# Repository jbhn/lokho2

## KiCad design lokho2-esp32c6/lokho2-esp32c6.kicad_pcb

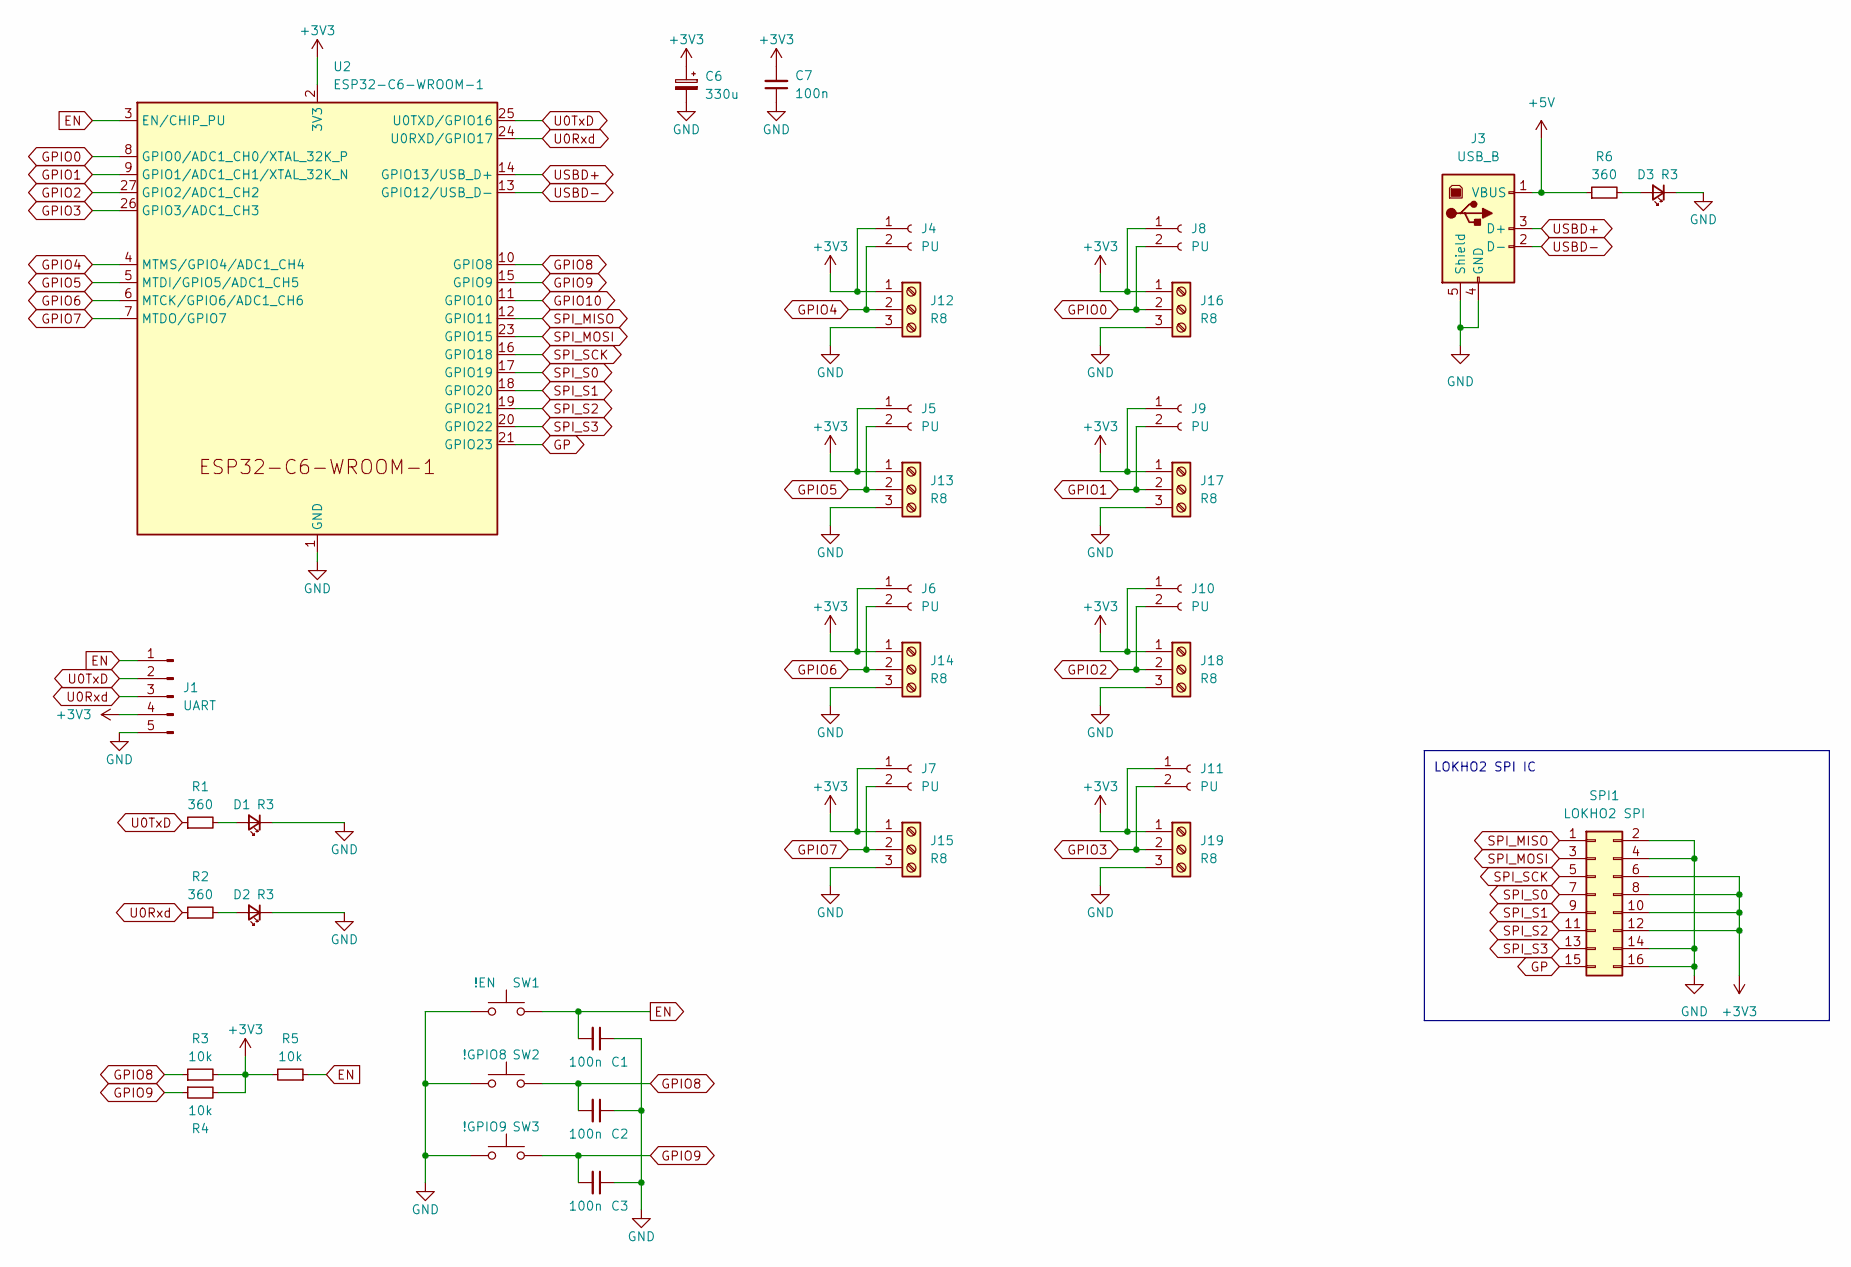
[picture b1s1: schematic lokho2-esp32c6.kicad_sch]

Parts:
C1, C2, C3, C7: 100n; C_Disc_D5.0mm_W2.5mm_P5.00mm
C6: 330u; CP_Radial_D8.0mm_P3.50mm
D1, D2, D3: R3; LED_D3.0mm
J1: UART; PinHeader_1x05_P2.54mm_Horizontal
J3: USB_B; USB_B_Lumberg_2411_02_Horizontal
J4, J5, J6, J7, J8, J9, J10, J11: PU; PinSocket_1x02_P2.54mm_Vertical
J12, J13, J14, J15, J16, J17, J18, J19: R8; TerminalBlock_4Ucon_1x03_P3.50mm_Horizontal
R1, R2, R6: 360; R_Axial_DIN0204_L3.6mm_D1.6mm_P7.62mm_Horizontal
R3, R4, R5: 10k; R_Axial_DIN0204_L3.6mm_D1.6mm_P7.62mm_Horizontal
SPI1: LOKHO2 SPI; IDC-Header_2x08_P2.54mm_Horizontal
SW1: !EN; SW_PUSH_6mm
SW2: !GPIO8; SW_PUSH_6mm
SW3: !GPIO9; SW_PUSH_6mm
U2: ESP32-C6-WROOM-1

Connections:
+3V3: C6.1, C7.2, J1.4, J4.1, J5.1, J6.1, J7.1, J8.1, J9.1, J10.1, J11.1, J12.1, J13.1, J14.1, J15.1, J16.1, J17.1, J18.1, J19.1, R3.2, R4.2, R5.2, SPI1.6, SPI1.8, SPI1.10, SPI1.12, U2.2 (3V3)
+5V: J3.1 (VBUS), R6.1
EN: C1.2, J1.1, R5.1, SW1.2, U2.3 (EN/CHIP_PU)
GND: C1.1, C2.1, C3.1, C6.2, C7.1, D1.1 (K), D2.1 (K), D3.1 (K), J1.5, J3.4 (GND), J3.5 (Shield), J12.3, J13.3, J14.3, J15.3, J16.3, J17.3, J18.3, J19.3, SPI1.2, SPI1.4, SPI1.14, SPI1.16, SW1.1, SW2.1, SW3.1, U2.1 (GND), U2.28 (GND), U2.29 (GND)
GP: SPI1.15, U2.21 (GPIO23)
GPIO0: J8.2, J16.2, U2.8 (GPIO0/ADC1_CH0/XTAL_32K_P)
GPIO1: J9.2, J17.2, U2.9 (GPIO1/ADC1_CH1/XTAL_32K_N)
GPIO2: J10.2, J18.2, U2.27 (GPIO2/ADC1_CH2)
GPIO3: J11.2, J19.2, U2.26 (GPIO3/ADC1_CH3)
GPIO4: J4.2, J12.2, U2.4 (MTMS/GPIO4/ADC1_CH4)
GPIO5: J5.2, J13.2, U2.5 (MTDI/GPIO5/ADC1_CH5)
GPIO6: J6.2, J14.2, U2.6 (MTCK/GPIO6/ADC1_CH6)
GPIO7: J7.2, J15.2, U2.7 (MTDO/GPIO7)
GPIO8: C2.2, R3.1, SW2.2, U2.10 (GPIO8)
GPIO9: C3.2, R4.1, SW3.2, U2.15 (GPIO9)
GPIO10: U2.11 (GPIO10)
unnamed: D1.2 (A), R1.2
unnamed: D2.2 (A), R2.2
unnamed: D3.2 (A), R6.2
SPI_MISO: SPI1.1, U2.12 (GPIO11)
SPI_MOSI: SPI1.3, U2.23 (GPIO15)
SPI_S0: SPI1.7, U2.17 (GPIO19)
SPI_S1: SPI1.9, U2.18 (GPIO20)
SPI_S2: SPI1.11, U2.19 (GPIO21)
SPI_S3: SPI1.13, U2.20 (GPIO22)
SPI_SCK: SPI1.5, U2.16 (GPIO18)
U0Rxd: J1.3, R2.1, U2.24 (U0RXD/GPIO17)
U0TxD: J1.2, R1.1, U2.25 (U0TXD/GPIO16)
USBD+: J3.3 (D+), U2.14 (GPIO13/USB_D+)
USBD-: J3.2 (D-), U2.13 (GPIO12/USB_D-)

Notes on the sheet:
LOKHO2 SPI IC

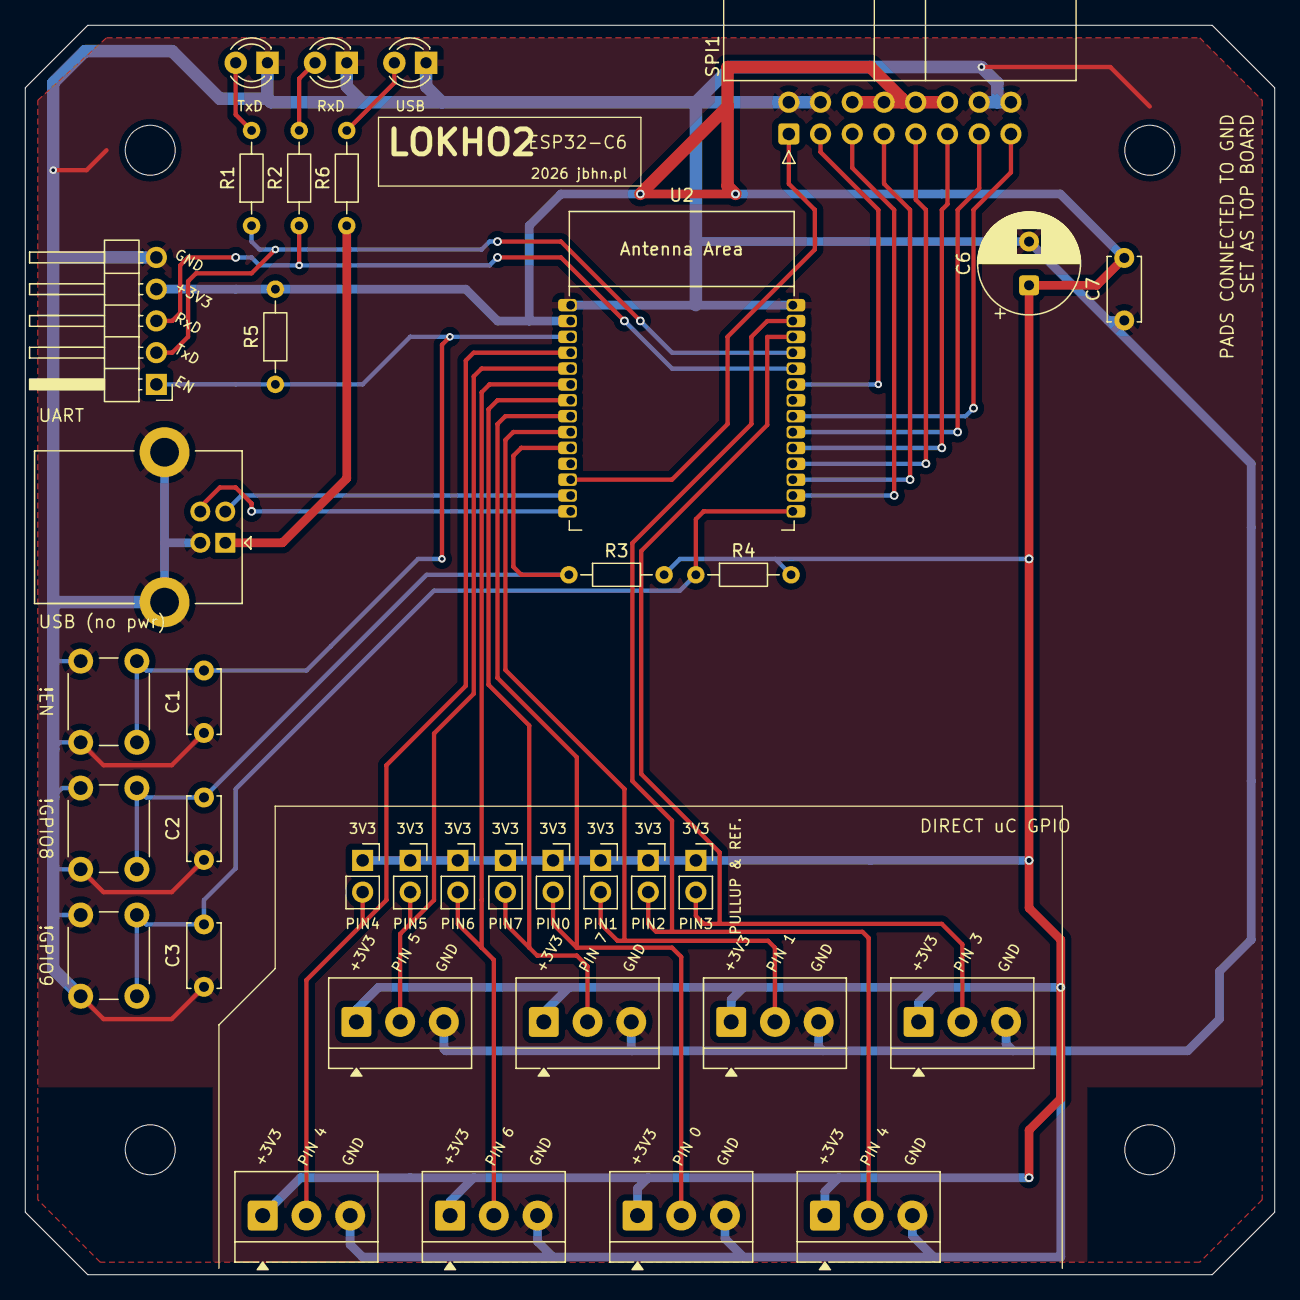
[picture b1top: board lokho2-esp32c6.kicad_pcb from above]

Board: 2 copper layers, 100.0 x 100.0 mm, 37 parts (0 on the bottom side), 29 nets.

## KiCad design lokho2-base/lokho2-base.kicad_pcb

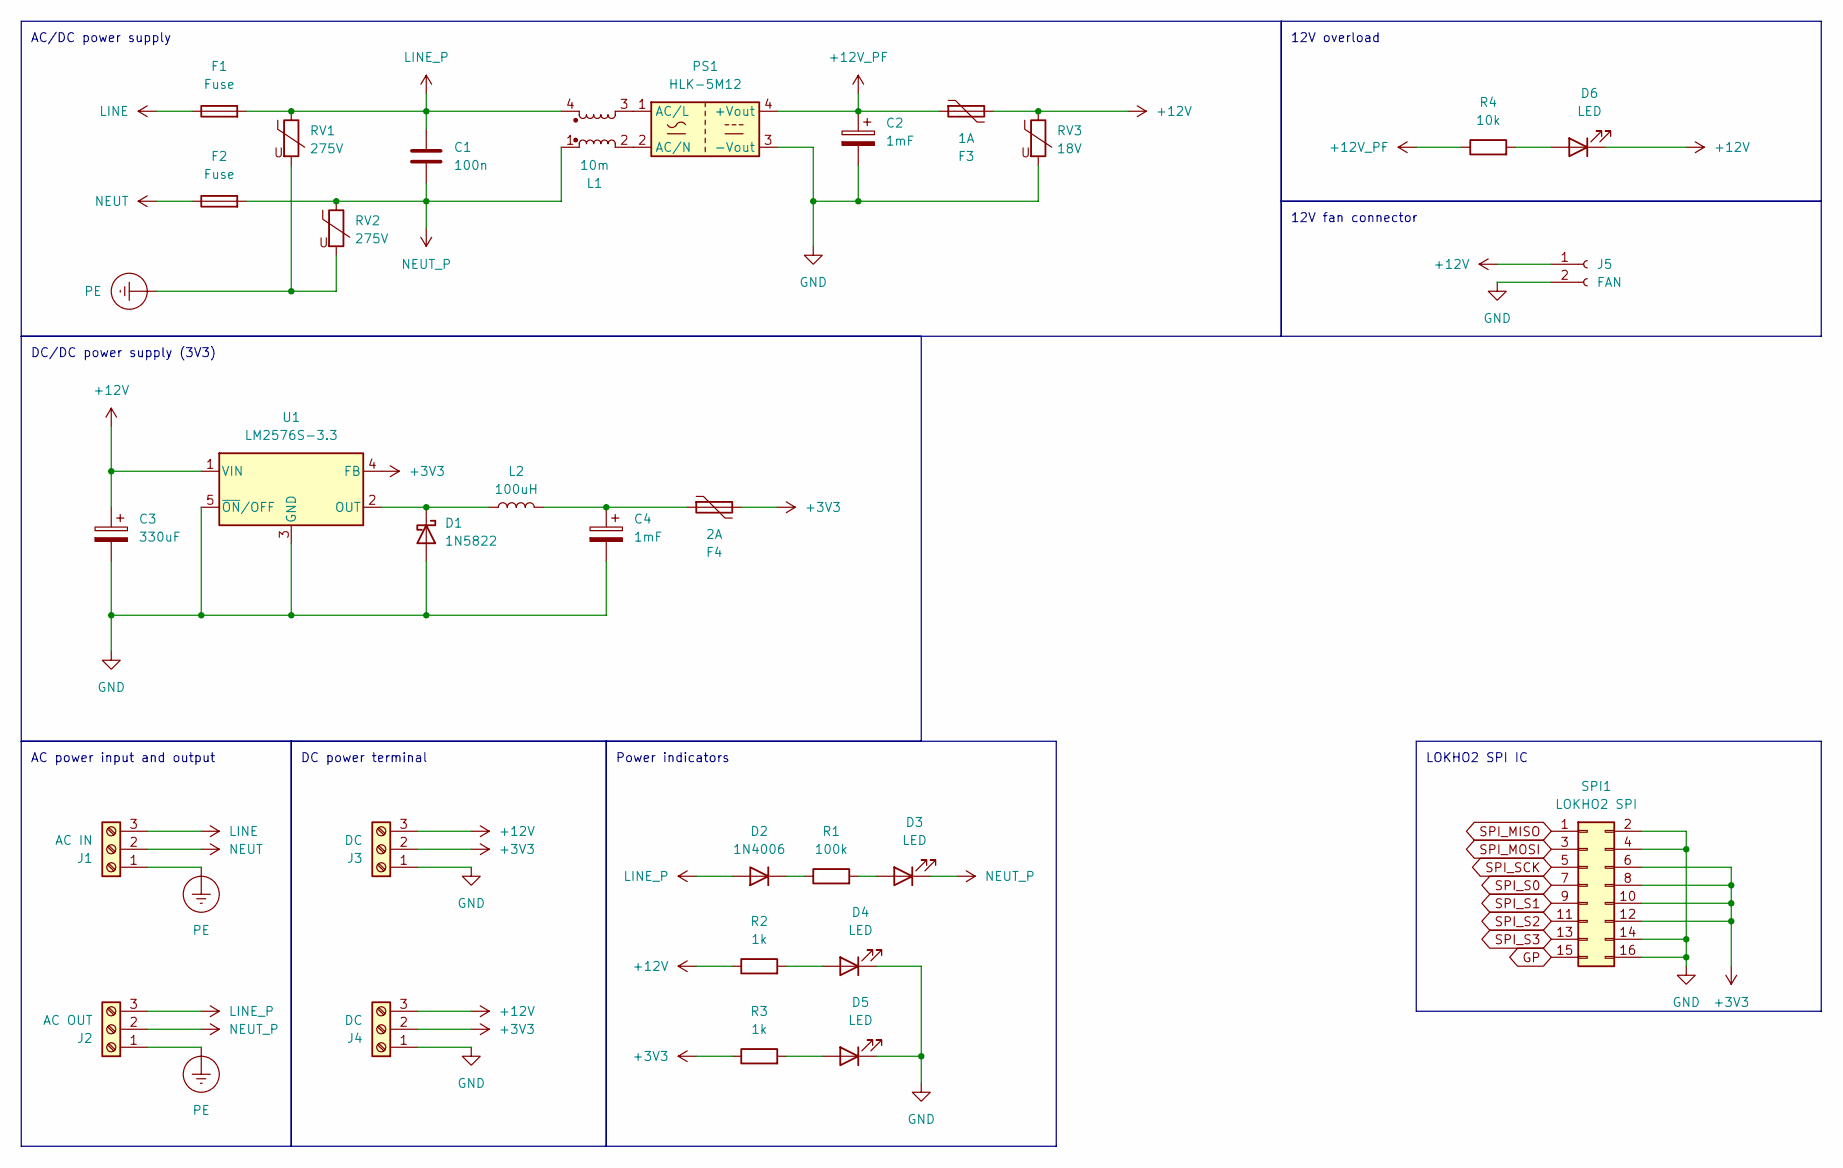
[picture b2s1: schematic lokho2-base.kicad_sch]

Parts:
C1: 100n; C_Rect_L11.5mm_W6.9mm_P10.00mm_MKT
C2, C4: 1mF; CP_Radial_D10.0mm_P5.00mm
C3: 330uF; CP_Radial_D8.0mm_P3.50mm
D1: 1N5822; D_DO-201AD_P15.24mm_Horizontal
D2: 1N4006; D_DO-41_SOD81_P10.16mm_Horizontal
D3, D4, D5: LED; LED_D3.0mm_Horizontal_O1.27mm_Z2.0mm
D6: LED; LED_D3.0mm
F1, F2: Fuse; Fuseholder_Clip-5x20mm_Littelfuse_100_Inline_P20.50x4.60mm_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
F3: 1A; C_Disc_D8.0mm_W2.5mm_P5.00mm
F4: 2A; C_Disc_D8.0mm_W2.5mm_P5.00mm
J1: AC IN; TerminalBlock_4Ucon_1x03_P3.50mm_Horizontal
J2: AC OUT; TerminalBlock_4Ucon_1x03_P3.50mm_Horizontal
J3, J4: DC; TerminalBlock_4Ucon_1x03_P3.50mm_Horizontal
J5: FAN; PinHeader_1x02_P2.54mm_Horizontal
L1: 10m; L_CommonMode_Toroid_Vertical_L22.0mm_W12.0mm_Px9.00mm_Py8.0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
L2: 100uH; L_Radial_D12.0mm_P5.00mm_Fastron_11P
PS1: HLK-5M12; Converter_ACDC_Hi-Link_HLK-5Mxx
R1: 100k; R_Axial_DIN0204_L3.6mm_D1.6mm_P7.62mm_Horizontal
R2, R3: 1k; R_Axial_DIN0204_L3.6mm_D1.6mm_P7.62mm_Horizontal
R4: 10k; R_Axial_DIN0204_L3.6mm_D1.6mm_P7.62mm_Horizontal
RV1, RV2: 275V; RV_Disc_D21.5mm_W4.3mm_P10mm
RV3: 18V; RV_Disc_D7mm_W3.4mm_P5mm
SPI1: LOKHO2 SPI; IDC-Header_2x08_P2.54mm_Horizontal
U1: LM2576S-3.3; TO-263-5_TabPin3

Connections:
+3V3: F4.2, J3.2, J4.2, R3.1, SPI1.6, SPI1.8, SPI1.10, SPI1.12, U1.4 (FB)
+12V: C3.1, D6.1 (K), F3.2, J3.3, J4.3, J5.1, R2.1, RV3.1, U1.1 (VIN)
+12V_PF: C2.1, F3.1, PS1.4 (+Vout), R4.1
GND: C2.2, C3.2, C4.2, D1.2 (A), D4.1 (K), D5.1 (K), J3.1, J4.1, J5.2, PS1.3 (-Vout), RV3.2, SPI1.2, SPI1.4, SPI1.14, SPI1.16, U1.3 (GND), U1.5 (~ON/OFF)
GP: SPI1.15
LINE: F1.1, J1.3
LINE_P: C1.1, D2.2 (A), F1.2, J2.3, L1.4, RV1.1
NEUT: F2.1, J1.2
NEUT_P: C1.2, D3.1 (K), F2.2, J2.2, L1.1, RV2.1
unnamed: C4.1, F4.1, L2.2
unnamed: D1.1 (K), L2.1, U1.2 (OUT)
unnamed: D2.1 (K), R1.1
unnamed: D3.2 (A), R1.2
unnamed: D4.2 (A), R2.2
unnamed: D5.2 (A), R3.2
unnamed: D6.2 (A), R4.2
unnamed: L1.3, PS1.1 (AC/L)
unnamed: L1.2, PS1.2 (AC/N)
PE: J1.1, J2.1, RV1.2, RV2.2
SPI_MISO: SPI1.1
SPI_MOSI: SPI1.3
SPI_S0: SPI1.7
SPI_S1: SPI1.9
SPI_S2: SPI1.11
SPI_S3: SPI1.13
SPI_SCK: SPI1.5

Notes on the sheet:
DC power terminal
12V fan connector
DC/DC power supply (3V3)
AC/DC power supply
AC power input and output
LOKHO2 SPI IC
Power indicators
12V overload

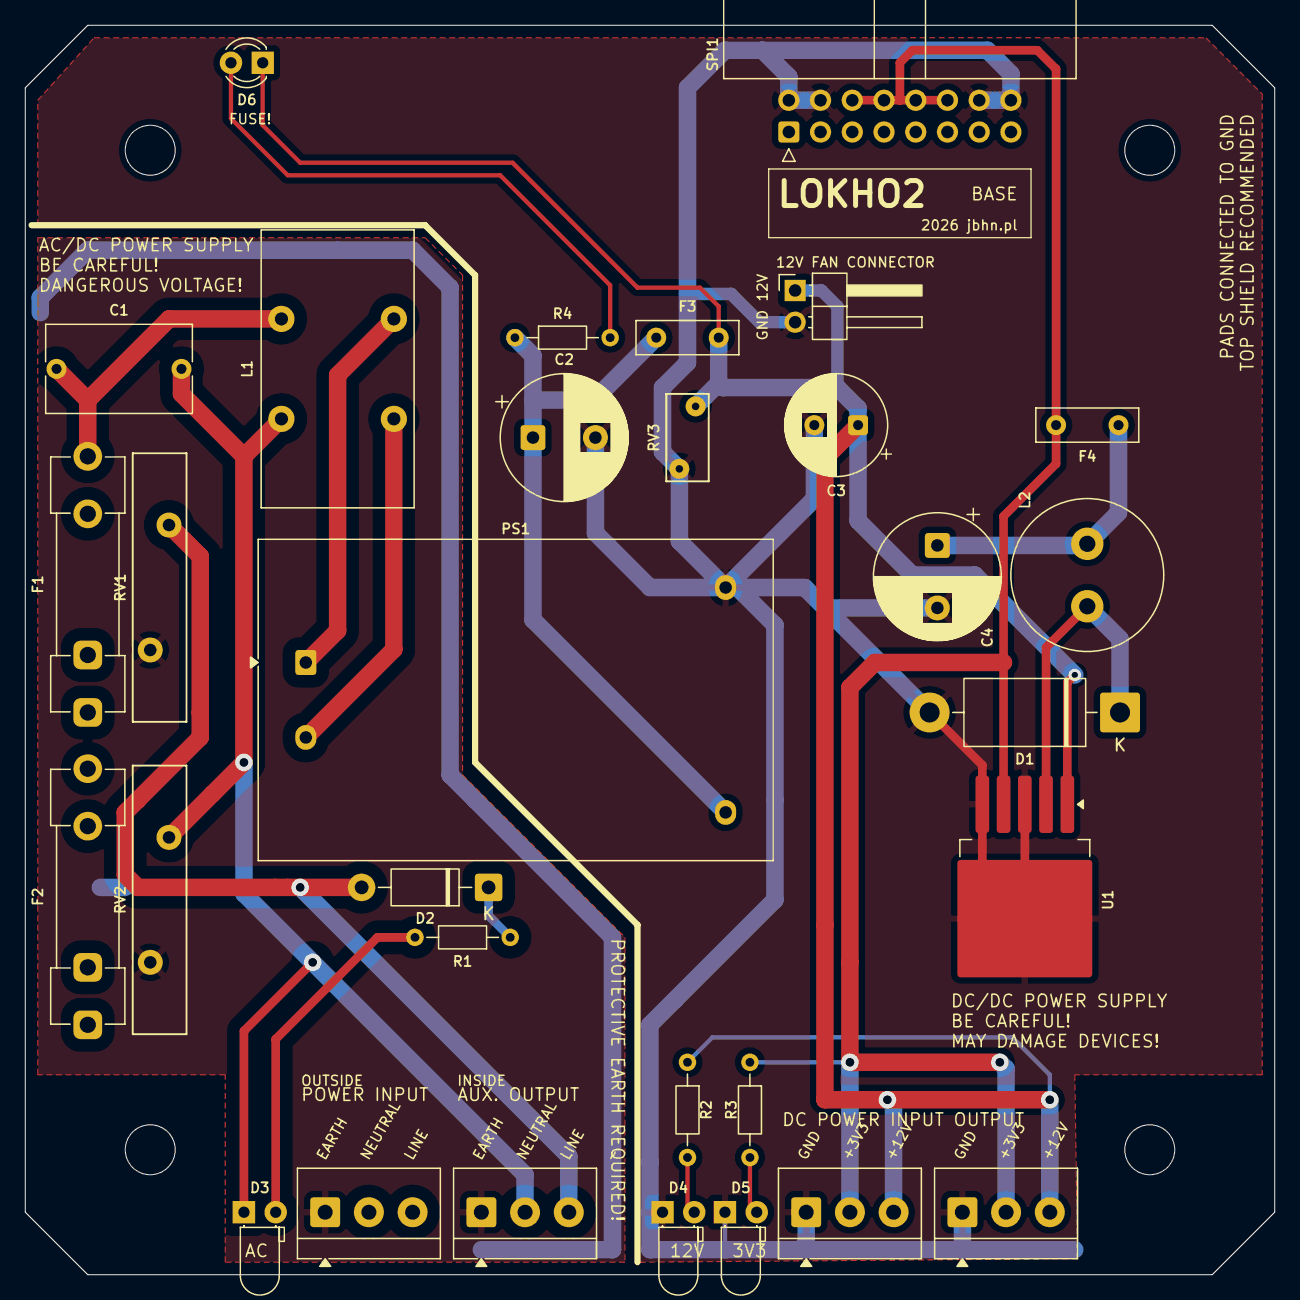
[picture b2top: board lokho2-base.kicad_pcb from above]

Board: 2 copper layers, 100.0 x 100.0 mm, 31 parts (0 on the bottom side), 18 nets.

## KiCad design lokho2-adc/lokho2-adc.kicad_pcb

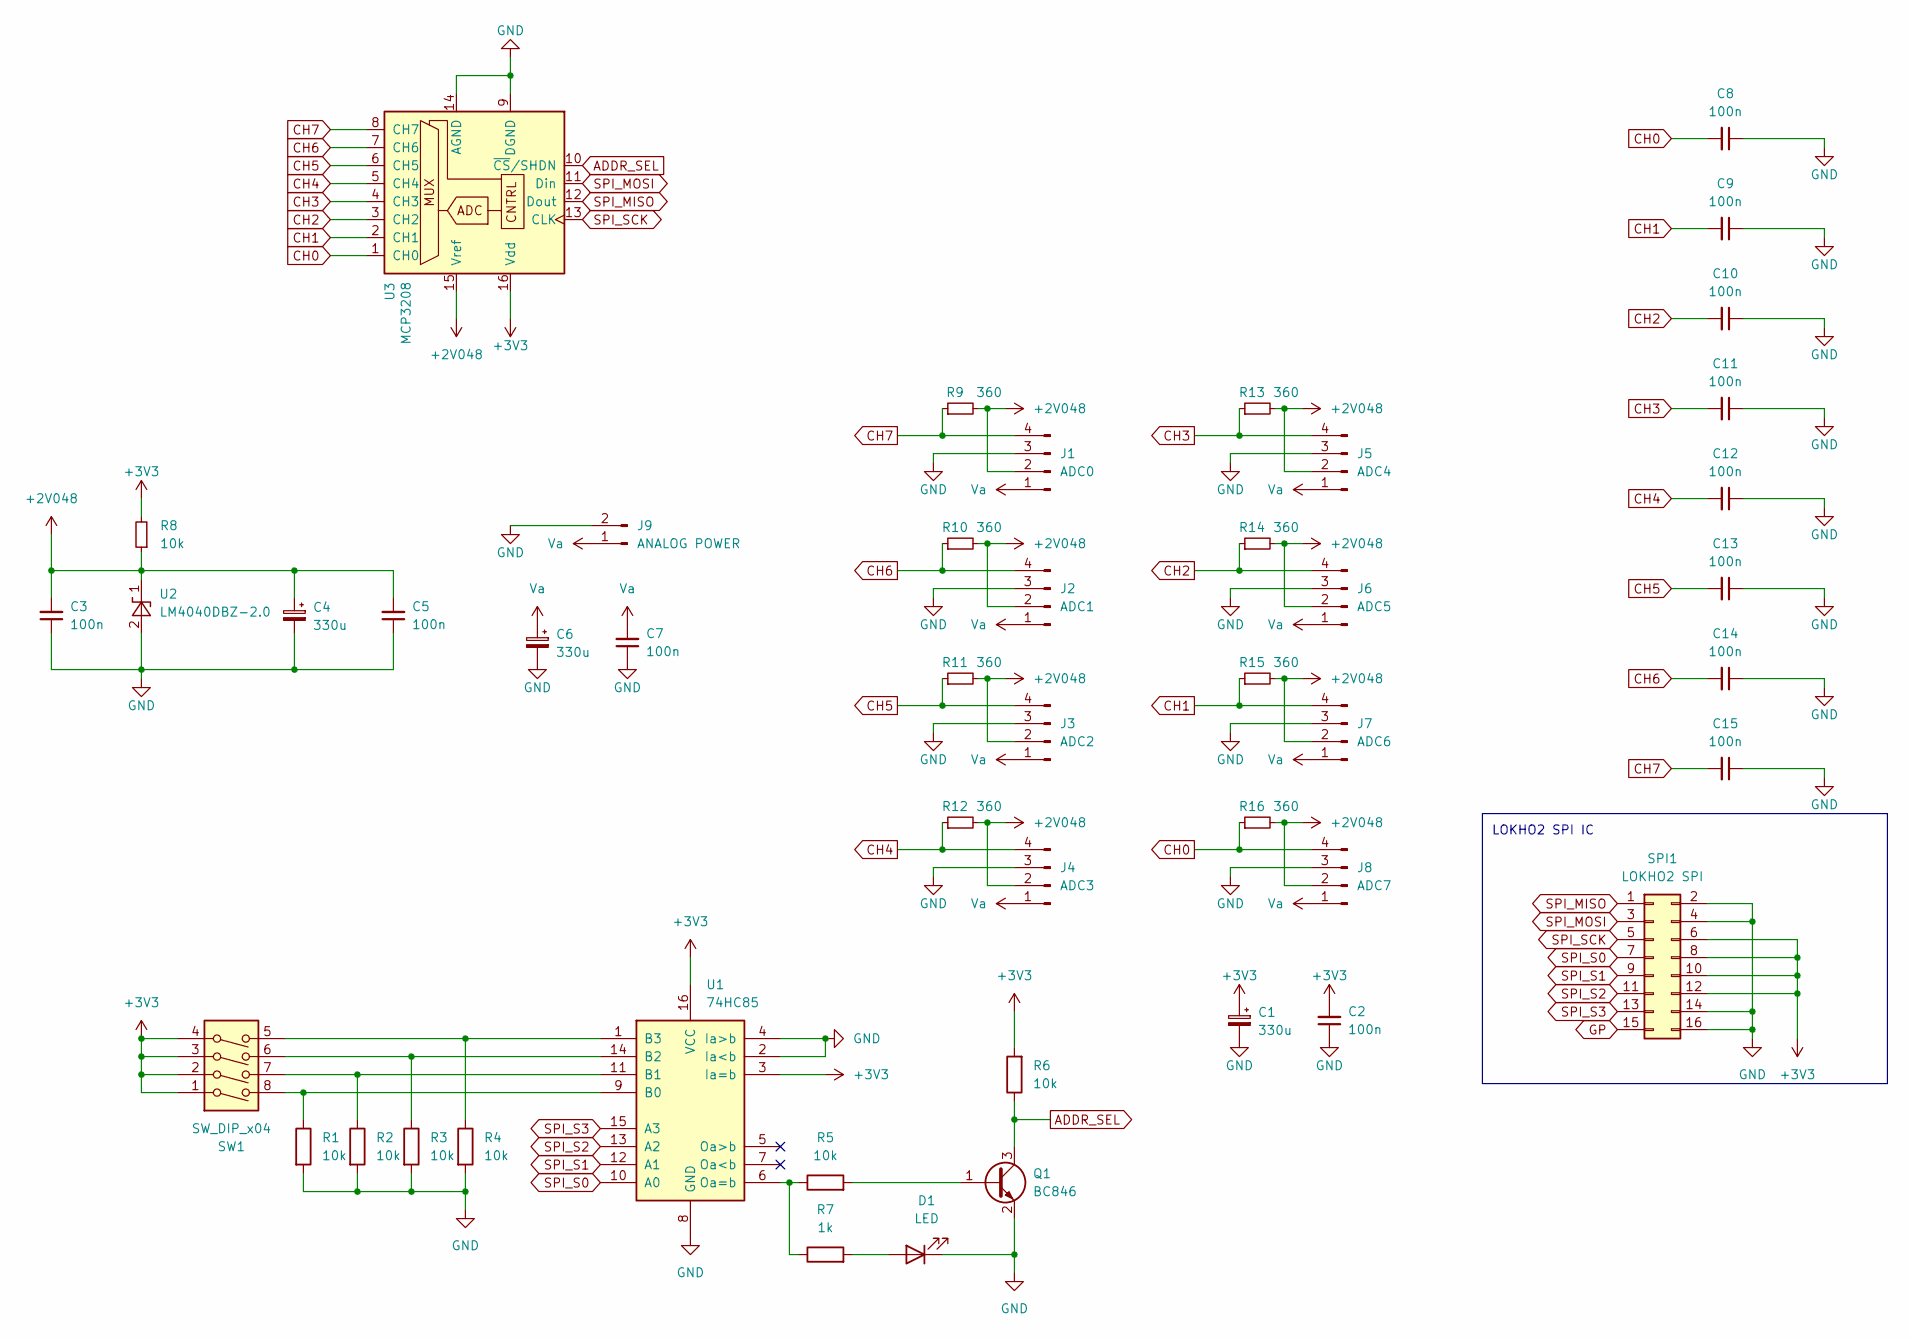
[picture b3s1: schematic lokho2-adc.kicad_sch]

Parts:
C1, C4, C6: 330u; CP_Radial_D8.0mm_P3.50mm
C2, C3, C5, C7: 100n; C_Disc_D5.0mm_W2.5mm_P5.00mm
C8, C9, C10, C11, C12, C13, C14, C15: 100n; C_Disc_D4.3mm_W1.9mm_P5.00mm
D1: LED; LED_D3.0mm
J1: ADC0; PinHeader_1x04_P2.54mm_Horizontal
J2: ADC1; PinHeader_1x04_P2.54mm_Horizontal
J3: ADC2; PinHeader_1x04_P2.54mm_Horizontal
J4: ADC3; PinHeader_1x04_P2.54mm_Horizontal
J5: ADC4; PinHeader_1x04_P2.54mm_Horizontal
J6: ADC5; PinHeader_1x04_P2.54mm_Horizontal
J7: ADC6; PinHeader_1x04_P2.54mm_Horizontal
J8: ADC7; PinHeader_1x04_P2.54mm_Horizontal
J9: ANALOG POWER; PinHeader_1x02_P2.54mm_Horizontal
Q1: BC846; SOT-23
R1, R2, R3, R4, R5, R6, R8: 10k; R_Axial_DIN0204_L3.6mm_D1.6mm_P7.62mm_Horizontal
R7: 1k; R_Axial_DIN0204_L3.6mm_D1.6mm_P7.62mm_Horizontal
R9, R10, R11, R12, R13, R14, R15, R16: 360; R_Axial_DIN0204_L3.6mm_D1.6mm_P7.62mm_Horizontal
SPI1: LOKHO2 SPI; IDC-Header_2x08_P2.54mm_Horizontal
SW1: SW_DIP_x04; SW_DIP_SPSTx04_Slide_6.7x11.72mm_W7.62mm_P2.54mm_LowProfile
U1: 74HC85; SO-16_3.9x9.9mm_P1.27mm
U2: LM4040DBZ-2.0; SOT-23
U3: MCP3208; DIP-16_W7.62mm_Socket

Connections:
+2V048: C3.2, C4.1, C5.2, J1.2, J2.2, J3.2, J4.2, J5.2, J6.2, J7.2, J8.2, R8.1, R9.2, R10.2, R11.2, R12.2, R13.2, R14.2, R15.2, R16.2, U2.1 (K), U3.15 (Vref)
+3V3: C1.1, C2.2, R6.2, R8.2, SPI1.6, SPI1.8, SPI1.10, SPI1.12, SW1.1, SW1.2, SW1.3, SW1.4, U1.3 (Ia=b), U1.16 (VCC), U3.16 (Vdd)
ADDR_SEL: Q1.3 (C), R6.1, U3.10 (~CS/SHDN)
CH0: C8.2, J8.4, R16.1, U3.1 (CH0)
CH1: C9.2, J7.4, R15.1, U3.2 (CH1)
CH2: C10.2, J6.4, R14.1, U3.3 (CH2)
CH3: C11.2, J5.4, R13.1, U3.4 (CH3)
CH4: C12.2, J4.4, R12.1, U3.5 (CH4)
CH5: C13.2, J3.4, R11.1, U3.6 (CH5)
CH6: C14.2, J2.4, R10.1, U3.7 (CH6)
CH7: C15.2, J1.4, R9.1, U3.8 (CH7)
GND: C1.2, C2.1, C3.1, C4.2, C5.1, C6.2, C7.1, C8.1, C9.1, C10.1, C11.1, C12.1, C13.1, C14.1, C15.1, D1.1 (K), J1.3, J2.3, J3.3, J4.3, J5.3, J6.3, J7.3, J8.3, J9.2, Q1.2 (E), R1.2, R2.2, R3.2, R4.2, SPI1.2, SPI1.4, SPI1.14, SPI1.16, U1.2 (Ia<b), U1.4 (Ia>b), U1.8 (GND), U2.2 (A), U3.9 (DGND), U3.14 (AGND)
GP: SPI1.15
unnamed: D1.2 (A), R7.2
unnamed: Q1.1 (B), R5.2
unnamed: R1.1, SW1.8, U1.9 (B0)
unnamed: R2.1, SW1.7, U1.11 (B1)
unnamed: R3.1, SW1.6, U1.14 (B2)
unnamed: R4.1, SW1.5, U1.1 (B3)
unnamed: R5.1, R7.1, U1.6 (Oa=b)
SPI_MISO: SPI1.1, U3.12 (Dout)
SPI_MOSI: SPI1.3, U3.11 (Din)
SPI_S0: SPI1.7, U1.10 (A0)
SPI_S1: SPI1.9, U1.12 (A1)
SPI_S2: SPI1.11, U1.13 (A2)
SPI_S3: SPI1.13, U1.15 (A3)
SPI_SCK: SPI1.5, U3.13 (CLK)
Va: C6.1, C7.2, J1.1, J2.1, J3.1, J4.1, J5.1, J6.1, J7.1, J8.1, J9.1

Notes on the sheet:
LOKHO2 SPI IC

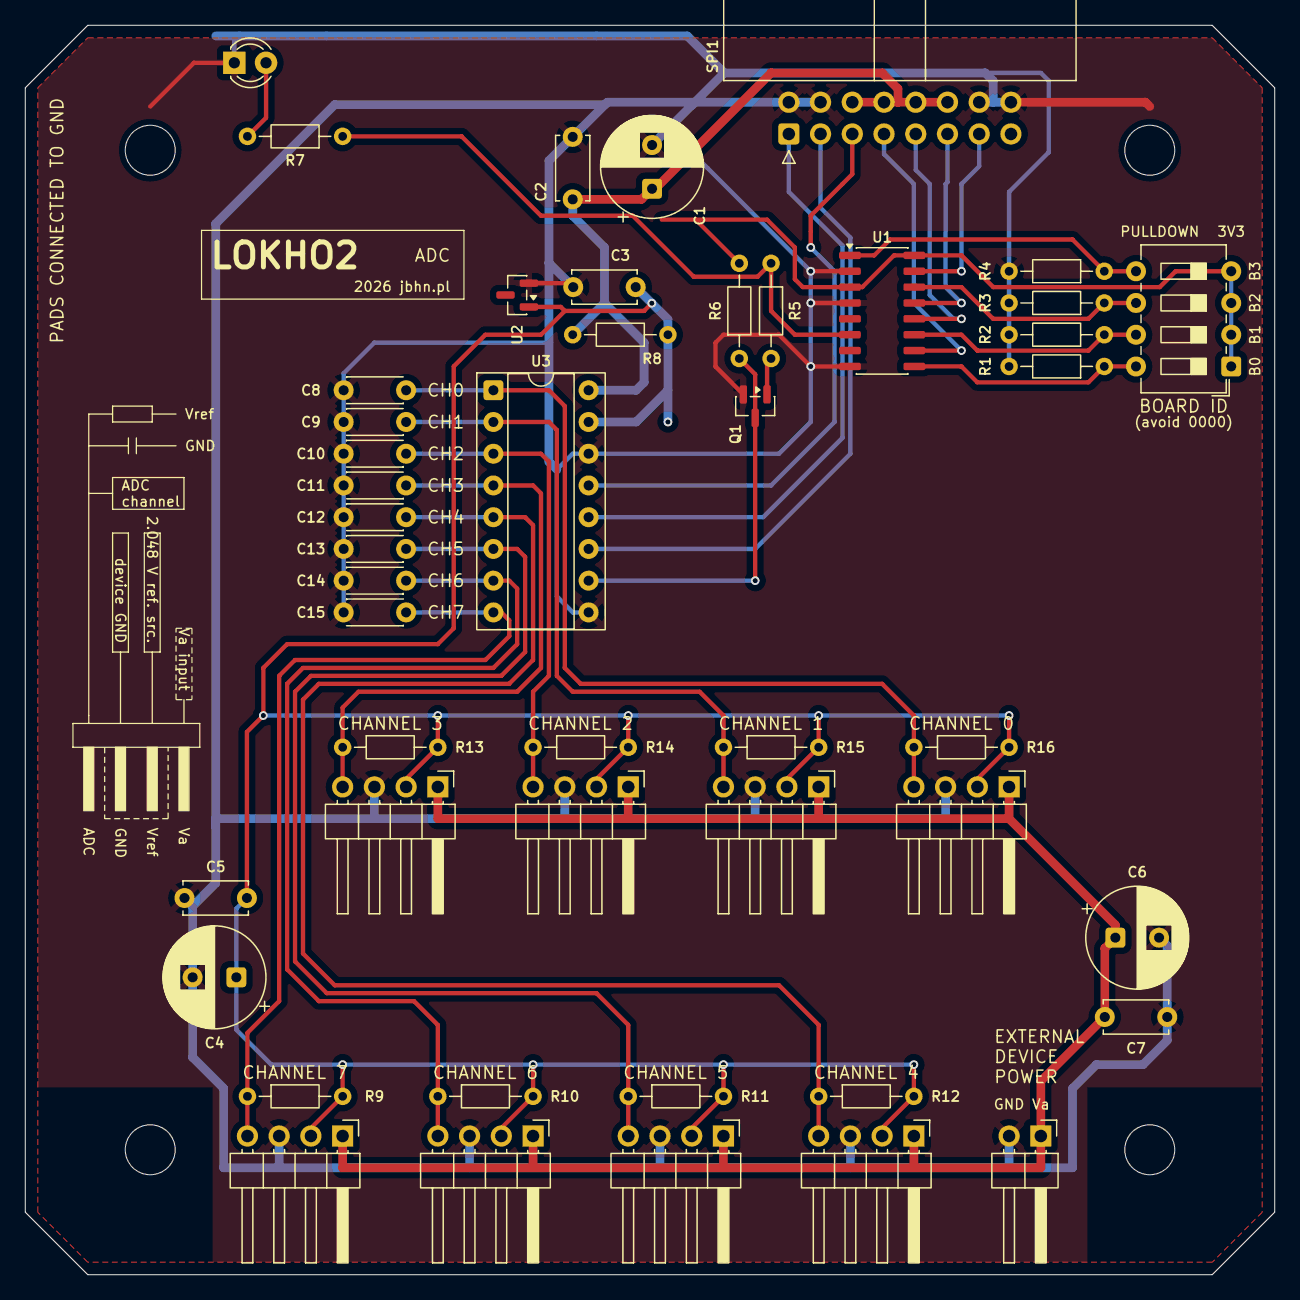
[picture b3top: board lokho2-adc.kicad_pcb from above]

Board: 2 copper layers, 100.0 x 100.0 mm, 47 parts (0 on the bottom side), 27 nets.

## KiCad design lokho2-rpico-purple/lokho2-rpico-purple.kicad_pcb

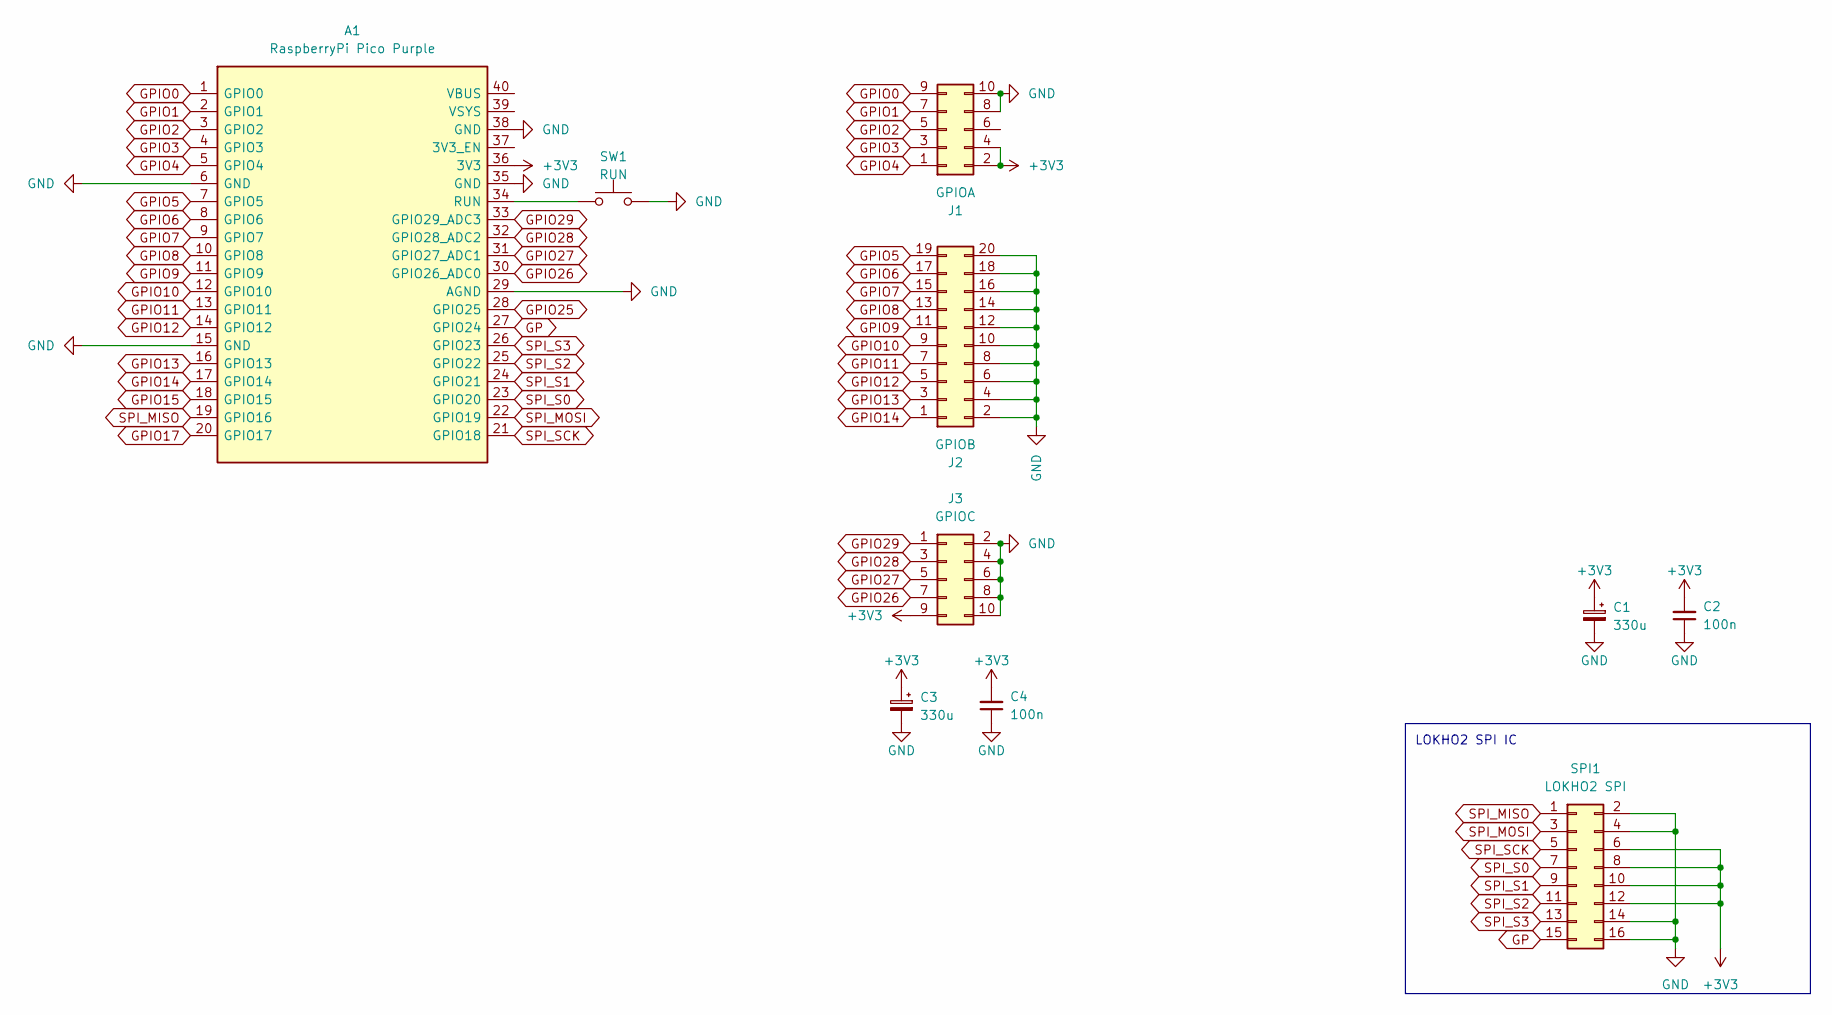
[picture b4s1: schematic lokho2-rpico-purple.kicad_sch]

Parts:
A1: RaspberryPi Pico Purple; RaspberryPi_Pico_Purple
C1, C3: 330u; CP_Radial_D8.0mm_P3.50mm
C2, C4: 100n; C_Disc_D5.0mm_W2.5mm_P5.00mm
J1: GPIOA; PinHeader_2x05_P2.54mm_Horizontal
J2: GPIOB; PinHeader_2x10_P2.54mm_Horizontal
J3: GPIOC; PinHeader_2x05_P2.54mm_Horizontal
SPI1: LOKHO2 SPI; IDC-Header_2x08_P2.54mm_Horizontal
SW1: RUN; SW_PUSH_6mm

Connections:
+3V3: A1.36 (3V3), C1.1, C2.2, C3.1, C4.2, J1.2, J1.4, J3.9, SPI1.6, SPI1.8, SPI1.10, SPI1.12
GND: A1.6 (GND), A1.15 (GND), A1.29 (AGND), A1.35 (GND), A1.38 (GND), C1.2, C2.1, C3.2, C4.1, J1.8, J1.10, J2.2, J2.4, J2.6, J2.8, J2.10, J2.12, J2.14, J2.16, J2.18, J2.20, J3.2, J3.4, J3.6, J3.8, J3.10, SPI1.2, SPI1.4, SPI1.14, SPI1.16, SW1.1
GP: A1.27 (GPIO24), SPI1.15
GPIO0: A1.1 (GPIO0), J1.9
GPIO1: A1.2 (GPIO1), J1.7
GPIO2: A1.3 (GPIO2), J1.5
GPIO3: A1.4 (GPIO3), J1.3
GPIO4: A1.5 (GPIO4), J1.1
GPIO5: A1.7 (GPIO5), J2.19
GPIO6: A1.8 (GPIO6), J2.17
GPIO7: A1.9 (GPIO7), J2.15
GPIO8: A1.10 (GPIO8), J2.13
GPIO9: A1.11 (GPIO9), J2.11
GPIO10: A1.12 (GPIO10), J2.9
GPIO11: A1.13 (GPIO11), J2.7
GPIO12: A1.14 (GPIO12), J2.5
GPIO13: A1.16 (GPIO13), J2.3
GPIO14: A1.17 (GPIO14), J2.1
GPIO15: A1.18 (GPIO15)
GPIO17: A1.20 (GPIO17)
GPIO25: A1.28 (GPIO25)
GPIO26: A1.30 (GPIO26_ADC0), J3.7
GPIO27: A1.31 (GPIO27_ADC1), J3.5
GPIO28: A1.32 (GPIO28_ADC2), J3.3
GPIO29: A1.33 (GPIO29_ADC3), J3.1
unnamed: A1.34 (RUN), SW1.2
SPI_MISO: A1.19 (GPIO16), SPI1.1
SPI_MOSI: A1.22 (GPIO19), SPI1.3
SPI_S0: A1.23 (GPIO20), SPI1.7
SPI_S1: A1.24 (GPIO21), SPI1.9
SPI_S2: A1.25 (GPIO22), SPI1.11
SPI_S3: A1.26 (GPIO23), SPI1.13
SPI_SCK: A1.21 (GPIO18), SPI1.5

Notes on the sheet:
LOKHO2 SPI IC

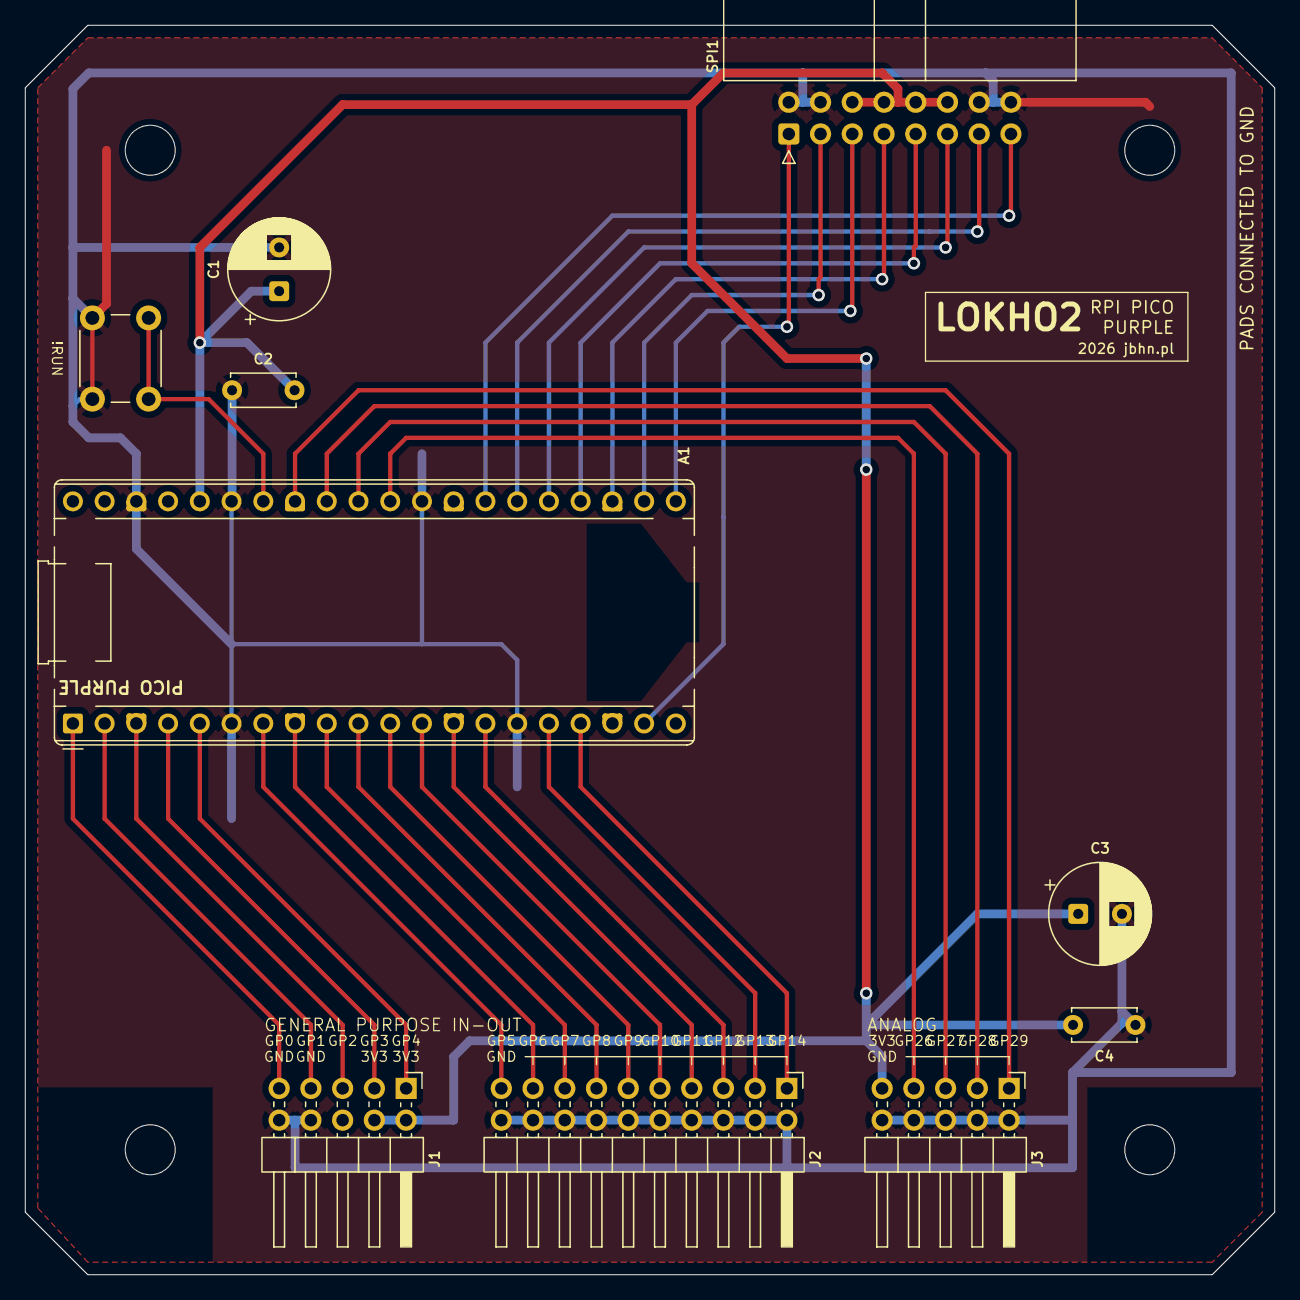
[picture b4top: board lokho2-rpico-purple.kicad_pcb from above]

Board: 2 copper layers, 100.0 x 100.0 mm, 10 parts (0 on the bottom side), 30 nets.
